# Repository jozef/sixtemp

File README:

NAME

    sixtemp_sensor.ino - read up to six 1-wire temperature sensors using
    Arduino and show their status using R(G)B led

SYNOPSIS

    See https://github.com/jozef/sixtemp_i2c for example and usage.

DESCRIPTION

    Arduino based sensor that can read up to six 1-wire DS18B20
    temperatures. Temperature sensors addresses are permanently stored in
    eeprom so that same positions are assigned between power-cycles. It
    provides the temperature readings via I2C interface and it also shows
    the temperature using 6xred-blue leds.

 I2C SLAVE device

    Connected to I2C, by default, responds on 0x18 address.

    First I2C master has to send one byte which is the read/write address.
    Addresses are:

        0x01        led on/off bool flag
        0x21        set led on/off flag. second byte is flag value
        0x60        read 1 byte with number of sensors
        0x61..0x66  read 14 bytes of sensor 1..6 data:
                        struct sixtemp_sensor {
                            bool has_error;
                            bool has_address;
                            int16_t tdeg;
                            char address[8];
                        };

 SERIAL INTERFACE

    Using Arduino serial port:

        $ minicom --device /dev/ttyUSB1
        eeprom magic found: 6temp 0.02

    ^^^ start-up message in case if sensors and configuration was read
    successfully from eeprom.

  help/?

    Prints version and available commands:

        > ?
        6temp 0.02
        supported commands:
          temp            - show temperatures from all sensors
          forget idx      - forget sensor on position idx
          info            - show sram usage and configuration
          set i2c [num]   - set i2c address (0x18 is default)
          tled [num]      - do led blink test num times (1 is default)
          help/?          - print this help

  info

    Prints version and debug/info:

        > info
        6temp 0.02
        sram free: 1158
        current configuration:
            i2c_addr: 0x18
            i2c_register: 0x0

  temp

    Prints all available temparature sensor readings:

        > temp
        sensor 1/6 [286164122f910528]: ERROR
        sensor 2/6 [28ff3ff6a1160322]: 22.0 C
        sensor 3/6 [286164122e7c499a]: 24.0 C
        sensor 4/6 [286164122f88f163]: 24.0 C
        sensor 5/6 [28ffa59492160558]: ERROR
        sensor 6/6 [286164122f89682a]: 24.0 C

  forget

    Forget one temperature sensor:

        > forget 1
        temp address 1 forgotten
    
        > temp
        sensor 1/6: n/a
        sensor 2/6 [28ff3ff6a1160322]: 22.0 C
        sensor 3/6 [286164122e7c499a]: 24.0 C
        sensor 4/6 [286164122f88f163]: 24.0 C
        sensor 5/6 [28ffa59492160558]: ERROR
        sensor 6/6 [286164122f89682a]: 24.0 C

  set i2c

    Change I2C client address:

        > set i2c 0x20
        setting i2c address to: 0x20
    
        > info
        6temp 0.02
        sram free: 1158
        current configuration:
            i2c_addr: 0x20
            i2c_register: 0x0
    
        > set i2c
        setting i2c address to: 0x18

  tled

    Will fade-in/out red leds and sequentially (1 to 6) blink with both
    red/blue leds to test if all are wired correctly:

        > tled 2
        testing 1/2
        fade all in/out red
        blink red
         red 1
         red 2
         red 3
         red 4
         red 5
         red 6
        LED test.
        blink blue
         blue 1
         blue 2
         blue 3
         blue 4
         blue 5
         blue 6
        testing 2/2
        ...

INSTALL

    Clone the repository folder into sketchbook/sixtemp_sensor and upload
    to Arduino.

HARDWARE

    KiCad schemas and pcb-s can be found in KiCad/ folder.

    See https://blog.kutej.net/2019/03/sixtemp for pictures of the
    hardware.

SEE ALSO

    I2C master library: https://github.com/jozef/sixtemp_i2c

TODO

        - info count&show number of errors per sensor

LICENSE

    This is free software, licensed under the MIT License.

AUTHOR

        Jozef Kutej

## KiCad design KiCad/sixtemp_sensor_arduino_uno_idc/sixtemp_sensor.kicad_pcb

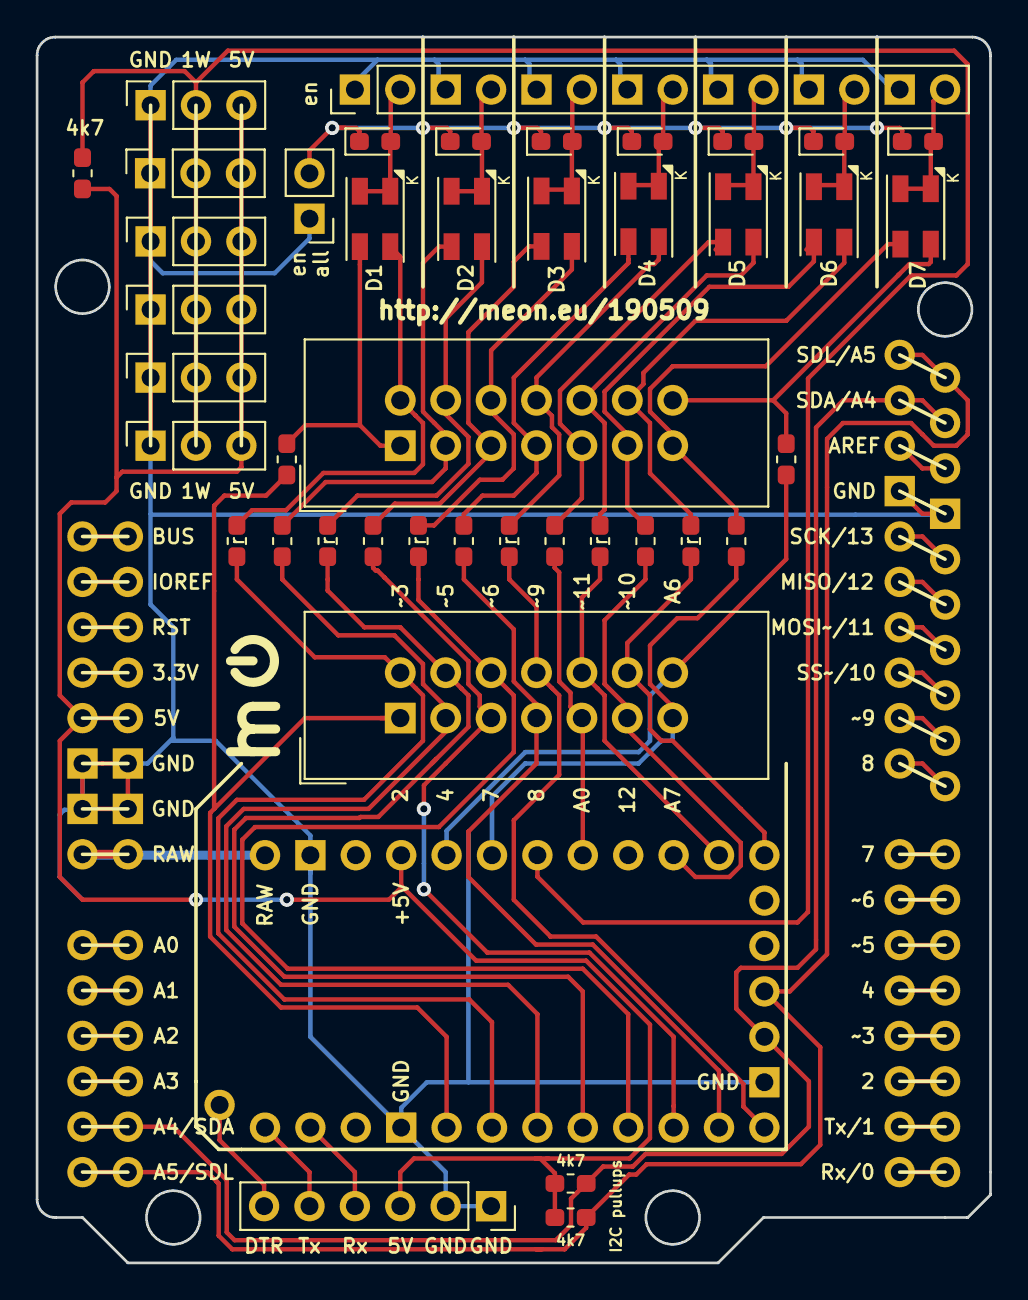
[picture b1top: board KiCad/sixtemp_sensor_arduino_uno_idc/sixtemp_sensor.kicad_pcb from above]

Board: 2 copper layers, 53.3 x 68.6 mm, 44 parts (0 on the bottom side), 45 nets.

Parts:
D1, D2, D3, D4, D5, D6, D7: LED_Dual_AACC; LED_WL_SBTW_PLCC4_2.4x2.4mm_P1.7mm
D19, D29, D39, D49, D59, D69, D79: D; D_0603_1608Metric_Pad1.05x0.95mm_HandSolder
J10: debug; PinSocket_1x06_P2.54mm_Vertical
J12: Sig_conn; IDC-Header_2x07_P2.54mm_Vertical
J13: RB_Conn; IDC-Header_2x07_P2.54mm_Vertical
J31, J32, J33, J34, J35, J36: 1-Wire; PinSocket_1x03_P2.54mm_Vertical
J123456: Led_EN; PinHeader_1x14_P2.54mm_Vertical
JP99: en_all; PinHeader_1x02_P2.54mm_Vertical
R11, R12, R21, R22, R31, R32, R41, R42, R51, R52, R61, R62, R71, R72: 1k; R_0603_1608Metric_Pad1.05x0.95mm_HandSolder
R81, R82, R101: 4k7; R_0603_1608Metric_Pad1.05x0.95mm_HandSolder
U1: Arduino_Pro_Mini_12_12_5_1; Shield_Arduino_Pro_Mini_12+12+5+1_pins
U2: Arduino_Uno_Black; Arduino_Uno_Black_2rows

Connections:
1wire: J31.2, J32.2, J33.2, J34.2, J35.2, J36.2, R101.1, U1.24
10_~SS~~: J12.12, R61.2, U1.14
11_MISO~~: J12.10, R51.2, U1.15
12_MISO: J12.11, R62.2, U1.16
+5V: J10.3, J31.3, J32.3, J33.3, J34.3, J35.3, J36.3, R81.1, R82.1, R101.2, U1.4, U2.6
A0: J12.9, R52.2, U1.23
A2: J12.13, R72.2, U1.25
A3: J12.14, R71.2, U1.26
D1_Blue: D1.2, J13.1, R12.1
D1_Red: D1.1, J13.2, R11.1
D2: J12.1, R12.2, U1.32
D2_Blue: D2.2, J13.3, R22.1
D2_Red: D2.1, J13.4, R21.1
D3_Blue: D3.2, J13.5, R32.1
D3_Red: D3.1, J13.6, R31.1
D3~~: J12.2, R11.2, U1.1
D4: J12.3, R22.2, U1.2
D4_Blue: D4.2, J13.7, R42.1
D4_Red: D4.1, J13.8, R41.1
D5_Blue: D5.2, J13.9, R52.1
D5_Red: D5.1, J13.10, R51.1
D5~~: J12.4, R21.2, U1.9
D6_Blue: D6.2, J13.11, R62.1
D6_Red: D6.1, J13.12, R61.1
D6~~: J12.6, R31.2, U1.10
D7: J12.5, R32.2, U1.11
D7_Blue: D7.2, J13.13, R72.1
D7_Red: D7.1, J13.14, R71.1
D8: J12.7, R42.2, U1.12
D9~~: J12.8, R41.2, U1.13
DTR: J10.6, U1.90
EN_D1: D1.3, D1.4, D19.2, J123456.2
EN_D2: D2.3, D2.4, D29.2, J123456.4
EN_D3: D3.3, D3.4, D39.2, J123456.6
EN_D4: D4.3, D4.4, D49.2, J123456.8
EN_D5: D5.3, D5.4, D59.2, J123456.10
EN_D6: D6.3, D6.4, D69.2, J123456.12
EN_D7: D7.3, D7.4, D79.2, J123456.14
GND: J10.1, J10.2, J31.1, J32.1, J33.1, J34.1, J35.1, J36.1, J123456.1, J123456.3, J123456.5, J123456.7, J123456.9, J123456.11, J123456.13, JP99.1, U1.3, U1.5, U1.21, U2.3, U2.5, U2.21
RAW: U1.99, U2.99
Rx: J10.4, U1.30
SCL: R82.2, U1.28, U2.28
SDA: R81.2, U1.27, U2.27
Tx: J10.5, U1.31
en_all_led: D19.1, D29.1, D39.1, D49.1, D59.1, D69.1, D79.1, JP99.2

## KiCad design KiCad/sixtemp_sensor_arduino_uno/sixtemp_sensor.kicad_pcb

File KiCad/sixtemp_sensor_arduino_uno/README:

needs: https://github.com/jozef/KiCad_Arduino_Shields

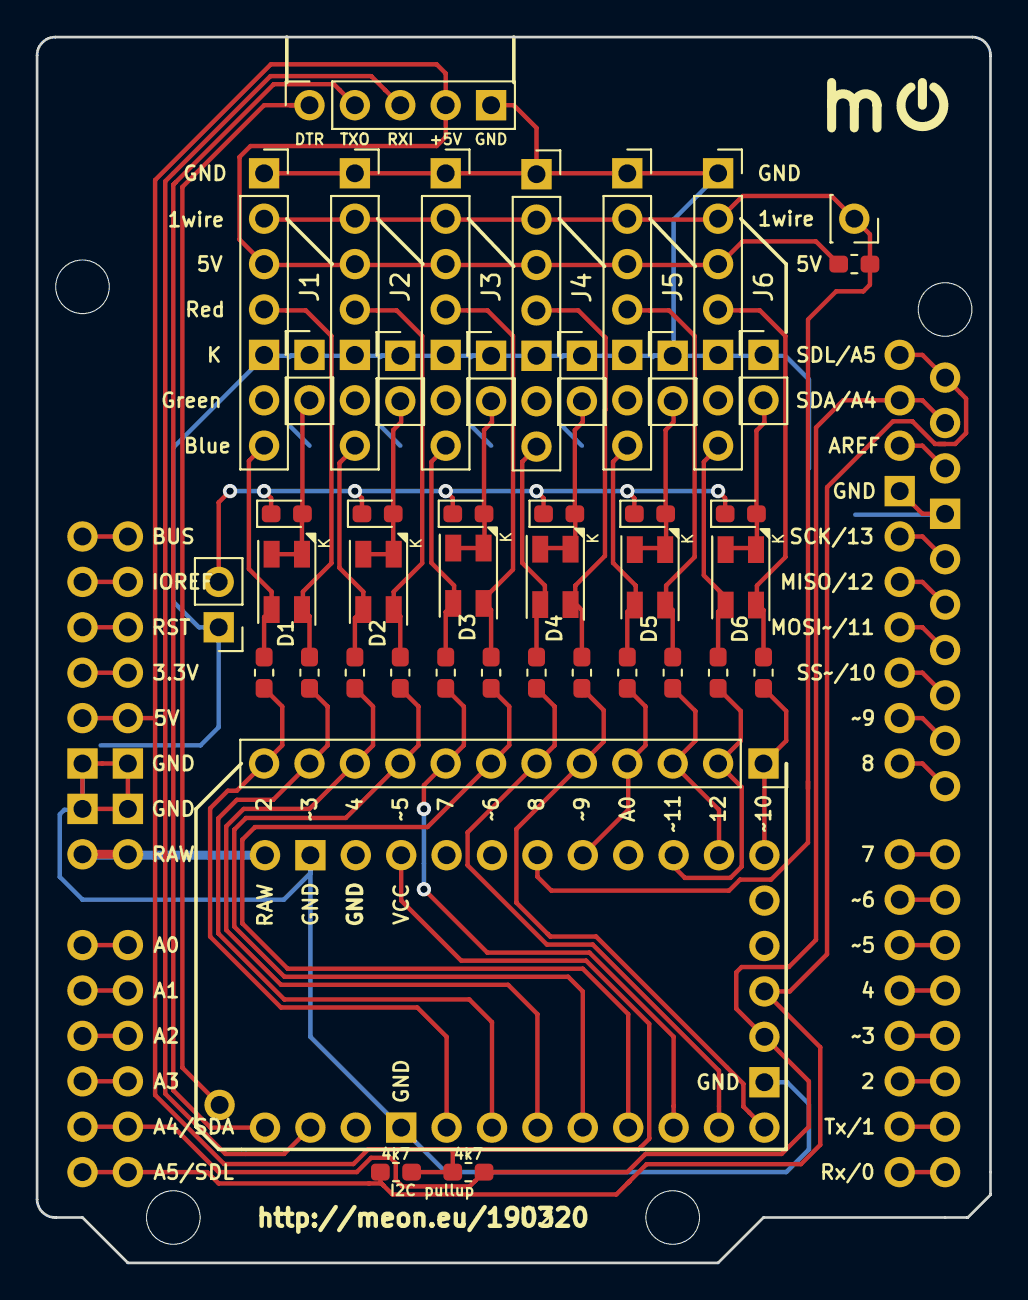
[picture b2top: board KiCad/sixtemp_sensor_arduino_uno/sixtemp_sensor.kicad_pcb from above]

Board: 2 copper layers, 53.3 x 68.6 mm, 45 parts (0 on the bottom side), 40 nets.

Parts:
D1, D2, D3, D4, D5, D6: LED_Dual_AACC; LED_WL_SBTW_PLCC4_2.4x2.4mm_P1.7mm
D19, D29, D39, D49, D59, D69: D; D_0603_1608Metric_Pad1.05x0.95mm_HandSolder
J1: 1W/D_6; PinSocket_1x07_P2.54mm_Vertical
J2: 1W/D_5; PinSocket_1x07_P2.54mm_Vertical
J3: 1W/D_4; PinSocket_1x07_P2.54mm_Vertical
J4, J6: 1W/D_1; PinSocket_1x07_P2.54mm_Vertical
J5: 1W/D_2; PinSocket_1x07_P2.54mm_Vertical
J8: 1wire; PinSocket_1x01_P2.54mm_Vertical
J10: debug; PinSocket_1x05_P2.54mm_Vertical
J12: Conn_01x12_Female; PinSocket_1x12_P2.54mm_Vertical
JP1, JP2, JP3, JP4, JP5, JP6, JP99: Jumper; PinHeader_1x02_P2.54mm_Vertical
R11, R12, R21, R22, R31, R32, R41, R42, R51, R52, R61, R62: 1k; R_0603_1608Metric_Pad1.05x0.95mm_HandSolder
R81, R82, R101: 4k7; R_0603_1608Metric_Pad1.05x0.95mm_HandSolder
U1: Arduino_Pro_Mini_12_12_5_1; Shield_Arduino_Pro_Mini_12+12+5+1_pins
U2: Arduino_Uno_Black; Arduino_Uno_Black_2rows

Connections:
1wire: J1.2, J2.2, J3.2, J4.2, J5.2, J6.2, J8.1, R101.1, U1.24
10_~SS~~: J12.1, R61.2, U1.14
11_MISO~~: J12.3, R51.2, U1.15
12_MISO: J12.2, R62.2, U1.16
+5V: J1.3, J2.3, J3.3, J4.3, J5.3, J6.3, J10.4, R81.1, R82.1, R101.2, U1.4, U2.6
A0: J12.4, R52.2, U1.23
D2: J12.12, R12.2, U1.32
D3~~: J12.11, R11.2, U1.1
D4: J12.10, R22.2, U1.2
D5~~: J12.9, R21.2, U1.9
D6~~: J12.7, R31.2, U1.10
D7: J12.8, R32.2, U1.11
D8: J12.6, R42.2, U1.12
D9~~: J12.5, R41.2, U1.13
GND: J1.1, J1.5, J2.1, J2.5, J3.1, J3.5, J4.1, J4.5, J5.1, J5.5, J6.1, J6.5, J10.5, JP1.1, JP2.1, JP3.1, JP4.1, JP5.1, JP6.1, JP99.1, U1.3, U1.5, U1.21, U2.3, U2.5, U2.21
unnamed: D1.1, J1.4, R11.1
unnamed: D1.2, J1.7, R12.1
unnamed: D1.3, D1.4, D19.2, JP1.2
unnamed: D2.1, J2.4, R21.1
unnamed: D2.2, J2.7, R22.1
unnamed: D2.3, D2.4, D29.2, JP2.2
unnamed: D3.1, J3.4, R31.1
unnamed: D3.2, J3.7, R32.1
unnamed: D3.3, D3.4, D39.2, JP3.2
unnamed: D4.1, J4.4, R41.1
unnamed: D4.2, J4.7, R42.1
unnamed: D4.3, D4.4, D49.2, JP4.2
unnamed: D5.1, J5.4, R51.1
unnamed: D5.2, J5.7, R52.1
unnamed: D5.3, D5.4, D59.2, JP5.2
unnamed: D6.1, J6.4, R61.1
unnamed: D6.2, J6.7, R62.1
unnamed: D6.3, D6.4, D69.2, JP6.2
unnamed: J10.1, U1.90
unnamed: J10.2, U1.31
unnamed: J10.3, U1.30
RAW: U1.99, U2.99
SCL: R82.2, U1.28, U2.28
SDA: R81.2, U1.27, U2.27
en_all_led: D19.1, D29.1, D39.1, D49.1, D59.1, D69.1, JP99.2

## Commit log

2017-12-22 initial
2017-12-29 add serial command to forget a temp sensor
2017-12-30 preparing for i2c
2017-12-30 add set i2c address
2017-12-30 s/crlf/lf/
2018-01-01 provide sensor values via i2c
2018-01-01 sixtemp.ino -> sixtemp_sensor.ino
2018-01-03 replace String with char* to save sram
2018-01-03 simplify cmds with spaces handling
2018-01-14 show i2c register
2018-01-14 provide README
2018-01-18 add led on/off option
2018-01-19 control config.led_on via i2c
2019-01-13 improve serial console
2019-03-11 use TextCMD from github
2019-03-13 190226 version of uno shield
2019-03-13 adapt to 3x new pins and spacial reorganization
2019-03-15 schematics with dtr pin and sidewise dtr/txo/rxi
2019-03-17 moving around pins
2019-03-18 connector for 2x6 pins, minimize via-s
2019-03-19 7 pins connectors instead of 4+3
2019-03-19 uno with 2 rows, 1x12 header for direct pwm+digital pins, full 5 pin debug header
2019-03-20 revert physical order of light leds
2019-03-28 cfg reset cmd, refresh 1w on temp, clean-up
2019-04-14 use int16_t for temperature instead of float
2019-04-16 first idc arduino shield version
2019-04-24 add seventh led diode & holes to use all of the pins
2019-05-05 add 2x i2c pullups
2019-05-09 update labels, different layout
2019-05-23 5->6 pin debug connector
2019-05-23 label resistors for red led
2019-05-24 A6→A3, A7→A2 and set as alarm
2019-05-25 update documentation
2019-05-25 draw lines between connected pin holes
